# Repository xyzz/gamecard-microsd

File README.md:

# PS Vita gamecard to microSD adapter

## Software

`driver` contains a kernel module. Add it to taihen's `config.txt` KERNEL section. You can download a precompiled `.skprx` from the [Releases](https://github.com/xyzz/gamecard-microsd/releases) section.

Your microSD card must have no partition table. exFAT filesystem should be written directly to the device. On Linux, do:

```
mkfs.exfat /dev/sdx # (without a number)
```

On Windows, this works: https://redd.it/6o4gqh / https://redd.it/6o62vx

On Mac this should work (Tested on OSX 10.12):

```
# List your attached storage, find your sd card
sudo DiskUtil list
# If necessary, unmount volume
sudo diskutil unmountdisk /dev/diskn (where n is the number of the mounted sd card)
# Format drive
sudo newfs_exfat -R /dev/diskn  
```

After that, the card still works on both Linux and Windows, however other devices might have some problems.

### Compiling the driver

To compile:

```
cd driver
mkdir build && cd build
cmake ..
make
```

## Hardware

`board` contains Autodesk EAGLE schematics and board files. **Note: last revision still untested.**

The pcb has to be 1mm thick. This means I only tested 1mm thick PCBs and found them to work fine. I don't know if other thicknesses work.

Note how the pcb has a hole in place of microsd socket. You need to flip the socket and mount it into the hole .

The socket should look like that. You can buy these from aliexpress for about $0.1-0.2/piece. Check out [issue 2](https://github.com/xyzz/gamecard-microsd/issues/2) for a buying guide.

There's no case for the adapter. Make sure to cover testpoints with some tape to prevent shorts. (v3.0 of the design has no test pads so you do not have to insulate anything). You also will have to use tweezers to remove adapter from PS Vita. Don't grab the adapter by the socket or you risk damaging it.

The adapter does not use Vita gamecard push-pull mechanism. If you feel a spring while inserting it, this means you are inserting it wrong.

If you accidentally short contacts, the Vita will power off. However, in my testing, this does not seem to cause any permanent damage.

Once you insert the adapter, you can replace microSD without taking the adapter out.

## Version history

### v3.0

* Reduced gamecard pads total width by 0.2mm.
* Removed testpads.
* Removed unused INS pad on the microSD socket side.
* Changed routing to reduce number of VIAs and the probability of electrons falling out of the board.

This design is not tested yet.

### v2.0

* Reduced gamecard pads total width by 1.0mm.
* Removed fourth microsd socket leg.

This design is not tested by me yet, but other people confirmed it works.

### v1.0

Original design.

## Alternative designs

You can find some alternative designs here:

* https://github.com/Gadorach/SD2VITA
* https://www.elotrolado.net/hilo_proyecto-hardmod-para-poner-un-lector-de-micro-sd-en-la-psvita_2229693 (Spanish)

(Send a pr if you want to be included here)

## License

Code inside the `driver` directory is licensed under GPLv3 or later.

Contents of the `board` directory are licensed under [CC0](https://creativecommons.org/publicdomain/zero/1.0/).

## Special thanks to

* @motoharu-gosuto for their work on gamecard RE
* @TheOfficialFlow for providing original version of the usbmc plugin

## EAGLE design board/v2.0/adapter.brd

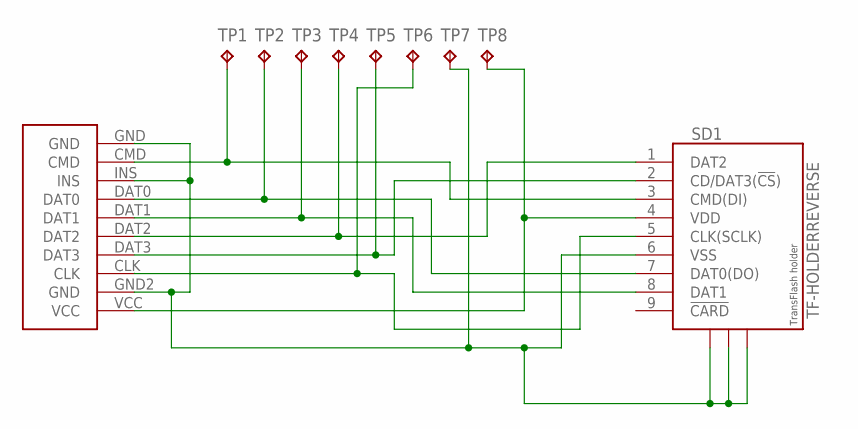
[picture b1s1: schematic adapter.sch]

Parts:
SD1: TF-HOLDERREVERSE; TF-PULL-REVERSE
TP1, TP2, TP3, TP4, TP5, TP6, TP7, TP8: TPTP20R; TP20R
U$1: CONNECTOR

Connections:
GND: SD1.6 (VSS), SD1.S1, SD1.S2, SD1.S3, TP7.TP, U$1.GND, U$1.GND2 (GND), U$1.INS
unnamed: SD1.4 (VDD), TP8.TP, U$1.VCC
unnamed: SD1.3 (CMD(DI)), TP1.TP, U$1.CMD
unnamed: SD1.7 (DAT0(DO)), TP2.TP, U$1.DAT0
unnamed: SD1.8 (DAT1), TP3.TP, U$1.DAT1
unnamed: SD1.1 (DAT2), TP4.TP, U$1.DAT2
unnamed: SD1.2 (CD/DAT3(!CS!)), TP5.TP, U$1.DAT3
unnamed: SD1.5 (CLK(SCLK)), TP6.TP, U$1.CLK

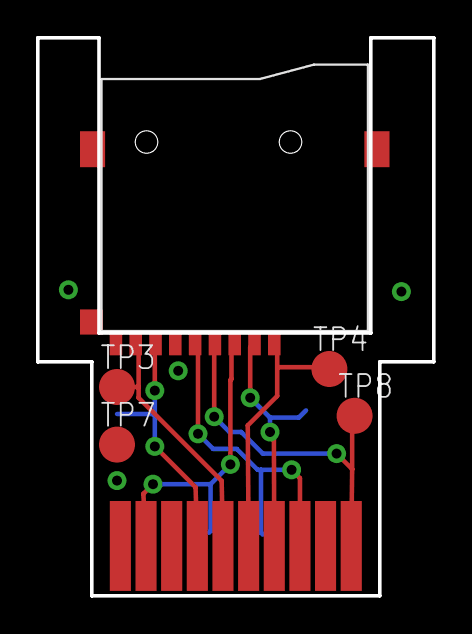
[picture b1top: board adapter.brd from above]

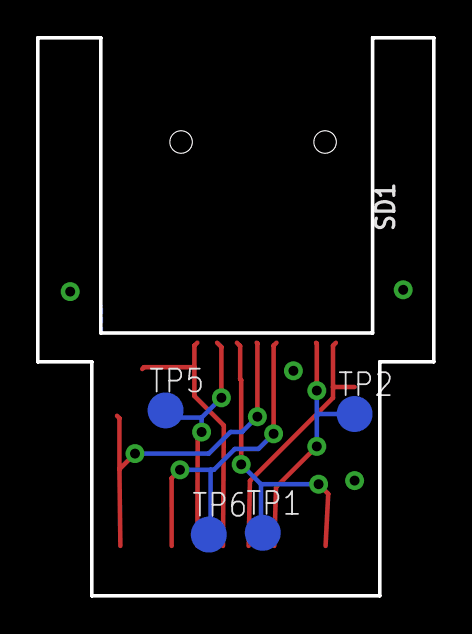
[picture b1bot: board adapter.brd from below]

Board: 2 copper layers, 22.0 x 31.0 mm, 10 parts (4 on the bottom side), 8 nets.

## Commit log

2017-06-30 initial
2017-06-30 Add board and readme
2017-06-30 fix a typo in readme
2017-06-30 add thickness
2017-07-05 add alternative designs section
2017-07-06 Added spanish website with all information
2017-07-12 Add CMake files to .gitignore
2017-07-12 Add instructions for compiling the plugin
2017-07-13 Added uma0 for Vita Memory Card
2017-07-15 Update thickness note
2017-07-19 Add v3.0
2017-07-19 Update readme with win format instructions.
2017-07-19 Update readme changelog
2017-08-09 Refactor MOUNT_POINT variable names
2017-08-09 Initial support for config file, still need to add support for mounting sdcard to uma0
2017-08-09 Enable redirect for gamecard and memcard to both ux0 and uma0
2017-08-09 Make kernel exports more generic
2017-08-10 Small bugfix
    Removing a duplicate call to io_remount()
2017-08-11 Fix headers
2017-08-11 Add license section
2017-09-11 Update README.md
    Added Mac formatting example
2018-03-11 Added 3.65/3.67 support
2018-06-17 Added support for firmware 3.68
2018-06-19 added appmgr patch two allow memory card remount
2018-06-19 Use tabs
2018-07-23 fix sporadic wakeups
2018-07-23 update license
2018-07-24 run dos2unix on all source files
2019-05-18 Added support for firmware 3.69/3.70
2019-08-04 Update readme with additional instructions for Mac
    Add some helpful commands to the readme that I needed when following the instructions
2019-08-26 Added support for FW 3.71
2019-08-31 Added support for FW 3.71/3.72
2019-12-27 Added support for FW 3.73
    thank you RealYoti for added support for 3.73
